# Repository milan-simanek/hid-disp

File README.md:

## HID display

This project is designed to show internal state of a head-less PC. It is an USB plug with 7-segment display. The software can show a number or a character to publish its state.

The PCB board contains 3.3V to 5V convertor, ATtiny MCU, shift register, 7-segment display and several passive components.

USB uses 3.3 signal levels while power line has 5V voltage. The device operates on 5V voltage so USB signal need to be converted to 3.3V by U3 (TXB0102DCU). 
The display is controlled by a shift register 74ACT164. The shift register provides up to 24mA current for the display (display HSDP-F513 requires 10mA per segment).
The display and USB protocol is driven by ATtiny MCU (U1).
PROG connector is used for firmware programming.

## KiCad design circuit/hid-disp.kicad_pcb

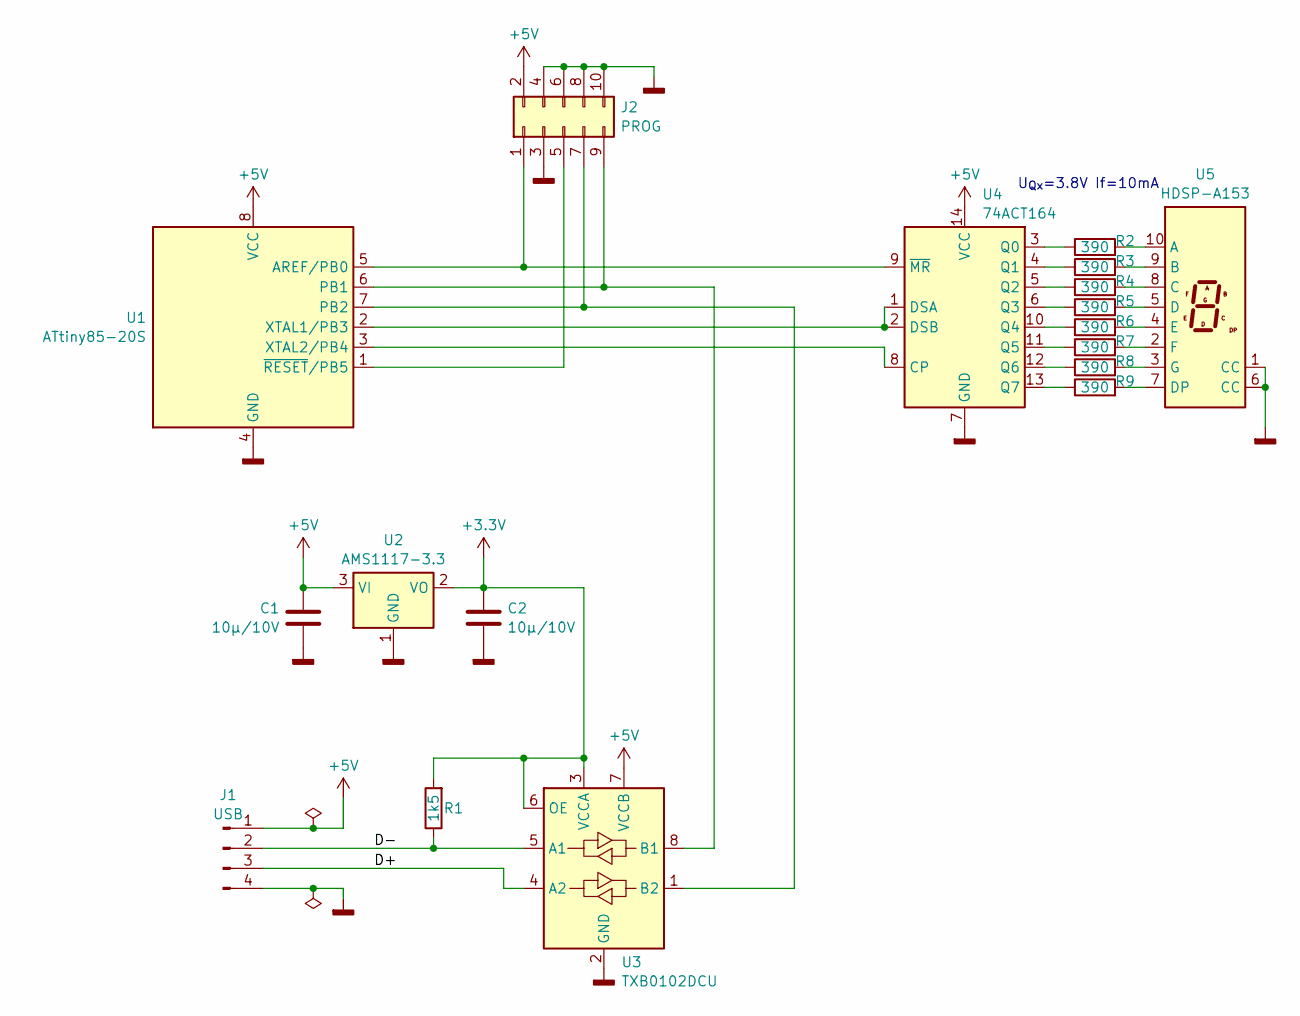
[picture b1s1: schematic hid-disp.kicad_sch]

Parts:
C1, C2: 10μ/10V; C_0603_1608Metric_Pad1.08x0.95mm_HandSolder
J1: USB; conn_USB-A_pcb
J2: PROG; Con2x5M
R1: 1k5; R_0402_1005Metric_Pad0.72x0.64mm_HandSolder
R2, R3, R4, R5, R6, R7, R8, R9: 390; R_0402_1005Metric_Pad0.72x0.64mm_HandSolder
U1: ATtiny85-20S; SOIC-8_5.3x5.3mm_P1.27mm
U2: AMS1117-3.3; SOT-223-3_TabPin2
U3: TXB0102DCU; VSSOP-8_2.3x2mm_P0.5mm
U4: 74ACT164; TSSOP-14_4.4x5mm_P0.65mm
U5: HDSP-A153; HDSP-A151

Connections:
+3.3V: C2.1, R1.2, U2.2 (VO), U3.3 (VCCA), U3.6 (OE)
+5V: C1.1, J1.1, J2.2, U1.8 (VCC), U2.3 (VI), U3.7 (VCCB), U4.14 (VCC)
/D+: J1.3, U3.4 (A2)
/D-: J1.2, R1.1, U3.5 (A1)
GNDD: C1.2, C2.2, J1.4, J2.3, J2.4, J2.6, J2.8, J2.10, U1.4 (GND), U2.1 (GND), U3.2 (GND), U4.7 (GND), U5.1 (CC), U5.6 (CC)
unnamed: J2.1, U1.5 (AREF/PB0), U4.9 (~MR)
unnamed: J2.5, U1.1 (~RESET/PB5)
unnamed: J2.7, U1.7 (PB2), U3.1 (B2)
unnamed: J2.9, U1.6 (PB1), U3.8 (B1)
unnamed: U1.2 (XTAL1/PB3), U4.1 (DSA), U4.2 (DSB)
unnamed: U1.3 (XTAL2/PB4), U4.8 (CP)
unnamed: R2.1, U4.3 (Q0)
unnamed: R3.1, U4.4 (Q1)
unnamed: R4.1, U4.5 (Q2)
unnamed: R5.1, U4.6 (Q3)
unnamed: R6.1, U4.10 (Q4)
unnamed: R7.1, U4.11 (Q5)
unnamed: R8.1, U4.12 (Q6)
unnamed: R9.1, U4.13 (Q7)
unnamed: R2.2, U5.10 (A)
unnamed: R3.2, U5.9 (B)
unnamed: R4.2, U5.8 (C)
unnamed: R5.2, U5.5 (D)
unnamed: R9.2, U5.7 (DP)
unnamed: R6.2, U5.4 (E)
unnamed: R7.2, U5.2 (F)
unnamed: R8.2, U5.3 (G)

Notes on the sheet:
If=10mA
U_{Qx}=3.8V

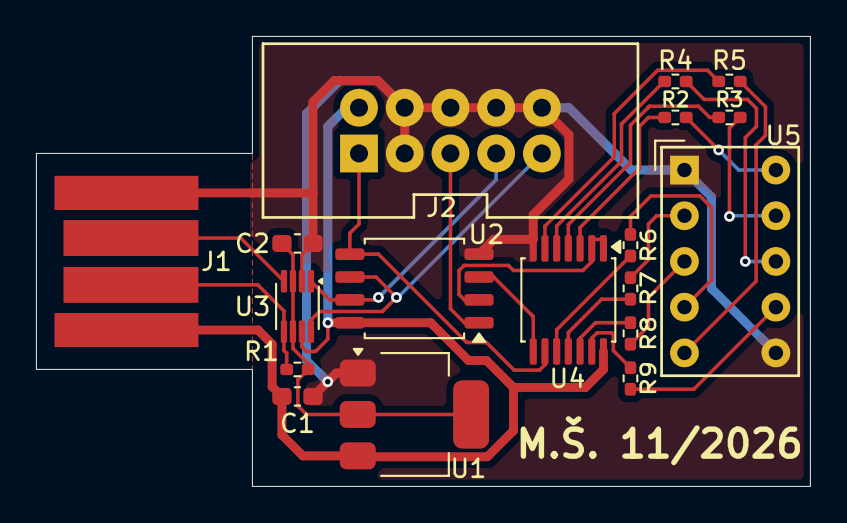
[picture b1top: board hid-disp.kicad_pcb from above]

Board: 2 copper layers, 43.0 x 25.0 mm, 18 parts (0 on the bottom side), 27 nets.
